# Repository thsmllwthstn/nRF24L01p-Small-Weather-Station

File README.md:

# Small Weather Station with nRF24L01+

For any nRF24L01+ project!

Vcc: 3.3V - 15V

### Description
Start a nRF24L01+ sensor network or expand your existing projects with this Small Weather Station!
This comes with easy to use example codes for Arduino and Raspberry Pi!

This station measures and sends:

 -Temperature
 
 -Humidity
 
 -Lightintensity

To achieve this the station uses three different sensors:

 -DS18B20: Digital temperature sensor
 
 -DHT11: Basic temperature and humidity sensor
 
 -LDR: Measures lightintensity

### What do you need?
You will need a Small Weather Station and your own nRF24L01+ receiver.
You can buy the Small Weather Station in the link below:

--ebay link

Or you can build your own station, you can find the schematics and source code in the link below:
https://github.com/thsmllwthstn/nRF24L01p-Small-Weather-Station/tree/master/station/station_basic

In the link below you will find an easy example code written for Arduino and Python 3 for receiving data from the station:
https://github.com/thsmllwthstn/nRF24L01p-Small-Weather-Station/tree/master/receiver

Simply copy and paste this code and you are ready to retreive data from the station!

### How does it work?
Power the Vin pin with 3V3 - 15V.

As soon as the onboard LED blinks 2 times in a row the station starts sending the data.

Use the example code to receive the data.

It sends the data every 5 seconds.

You can change the stations settings by pressing the button. The LED will go ON. The station is now in receiving mode.
There are 4 settings you can change:

 -Timer (rate at which the station sends the data in seconds)
 
 -Tranceive address
 
 -Receive address
 
 -Frequency

The example code explains in detail how to change these settings.

### Add a waterproof digital temperature sensor!
The station comes with 3 additional pins for connecting a waterproof DS18B20 temperature sensor.
Solder the Vcc, data and ground pins from the temperature sensor to the 3V3, data and GND pin from the station.
Once connected the station detects the presence of the added DS18B20 sensor.
The station will now send the standard readings with the added DS18B20 sensor!

### Programmable Small Weather Station?
Do you want full access to all the settings or use the station to control any other 3V3 circuit?
This is possible with a USBASP programmer and the programmable small weather station: 

--ebay link

Or you can build your own programmable station, you can find the schematics and source code in the link below:
https://github.com/thsmllwthstn/nRF24L01p-Small-Weather-Station/tree/master/station/station_basic_with_programmer

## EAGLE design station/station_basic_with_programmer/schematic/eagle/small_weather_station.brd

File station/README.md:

# Read me

Basic Small Weather Station:
--Foto1

Basic Small Weather Station with programmer:
--Foto2

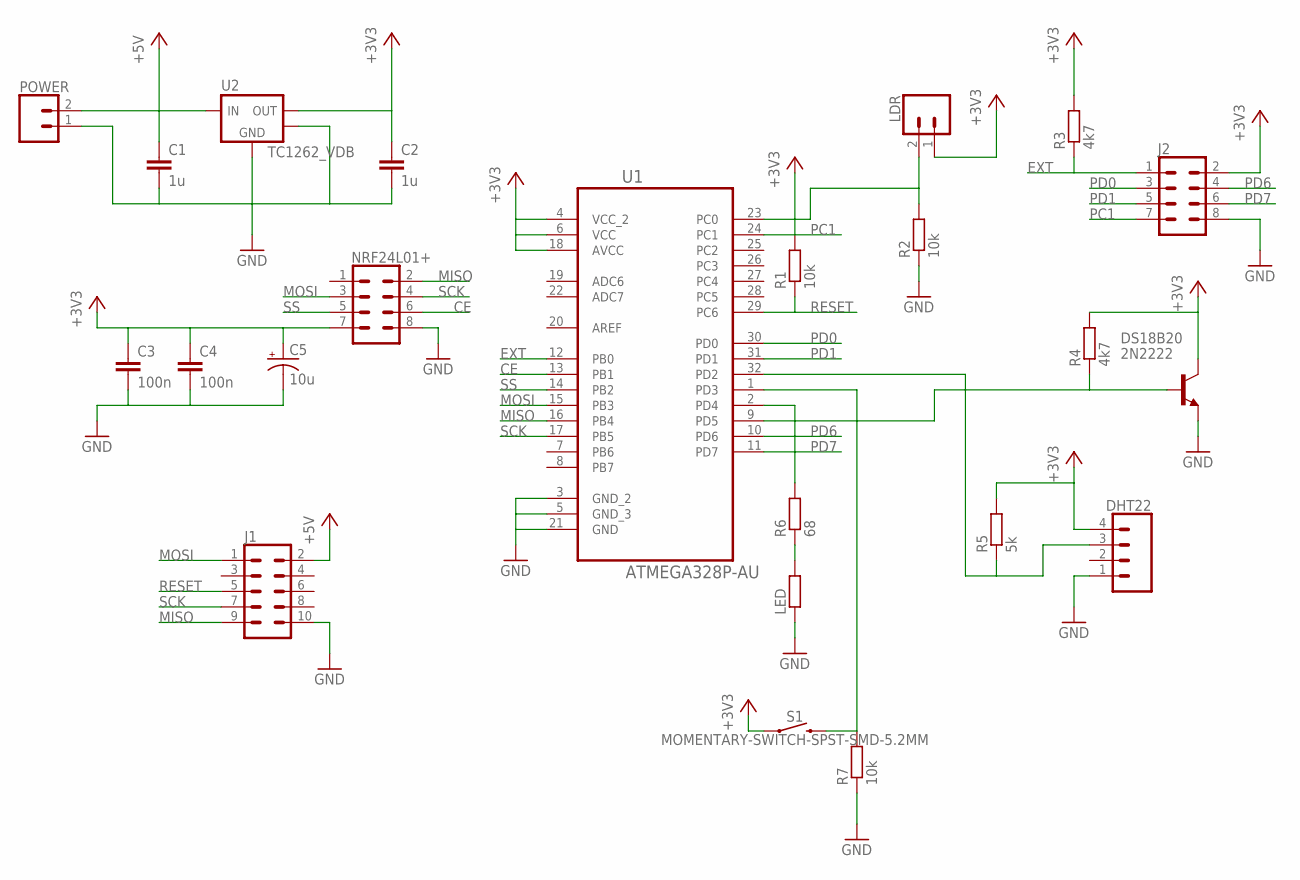
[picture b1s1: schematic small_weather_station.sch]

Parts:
C1, C2: 1u; C0402
C3, C4: 100n; C0402
C5: 10u; PANASONIC_D
DHT22: CONN_04; 1X04
DS18B20: 2N2222; TO92-EBC-OVAL
J1: CONN_05X2SHD-NS; 2X5-SHROUDED-NS
J2: CONN_04X2; 2X4
LDR: CONN_02; 1X02
LED: R-EU_R0402; R0402
NRF24L01+: CONN_04X2; 2X4
POWER: CONN_02; 1X02
R1, R2, R7: 10k; R0402
R3, R4: 4k7; R0402
R5: 5k; R0402
R6: 68; R0402
S1: MOMENTARY-SWITCH-SPST-SMD-5.2MM; TACTILE_SWITCH_SMD_5.2MM
U1: ATMEGA328P-AU; QFP80P900X900X120-32N
U2: TC1262_VDB; SOT-223-3

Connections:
+3V3: C2.1, C3.1, C4.1, C5.+, DHT22.4, DS18B20.C, J2.2, LDR.1, NRF24L01+.7, R1.2, R3.2, R4.2, R5.2, S1.1, U1.4 (VCC_2), U1.6 (VCC), U1.18 (AVCC), U2.3 (VOUT)
+5V: C1.1, J1.2, POWER.2, U2.1 (VIN)
CE: NRF24L01+.6, U1.13 (PB1)
EXT: J2.1, R3.1, U1.12 (PB0)
GND: C1.2, C2.2, C3.2, C4.2, C5.-, DHT22.1, DS18B20.E, J1.10, J2.8, LED.1, NRF24L01+.8, POWER.1, R2.1, R7.1, U1.3 (GND_2), U1.5 (GND_3), U1.21 (GND), U2.2 (GND), U2.4 (TAB)
MISO: J1.9, NRF24L01+.2, U1.16 (PB4)
MOSI: J1.1, NRF24L01+.3, U1.15 (PB3)
unnamed: R6.2, U1.2 (PD4)
unnamed: DHT22.3, R5.1, U1.32 (PD2)
unnamed: LDR.2, R2.2, U1.23 (PC0)
unnamed: DS18B20.B, R4.1, U1.9 (PD5)
unnamed: LED.2, R6.1
unnamed: R7.2, S1.3 (2), U1.1 (PD3)
PC1: J2.7, U1.24 (PC1)
PD0: J2.3, U1.30 (PD0)
PD1: J2.5, U1.31 (PD1)
PD6: J2.4, U1.10 (PD6)
PD7: J2.6, U1.11 (PD7)
RESET: J1.5, R1.1, U1.29 (PC6)
SCK: J1.7, NRF24L01+.4, U1.17 (PB5)
SS: NRF24L01+.5, U1.14 (PB2)

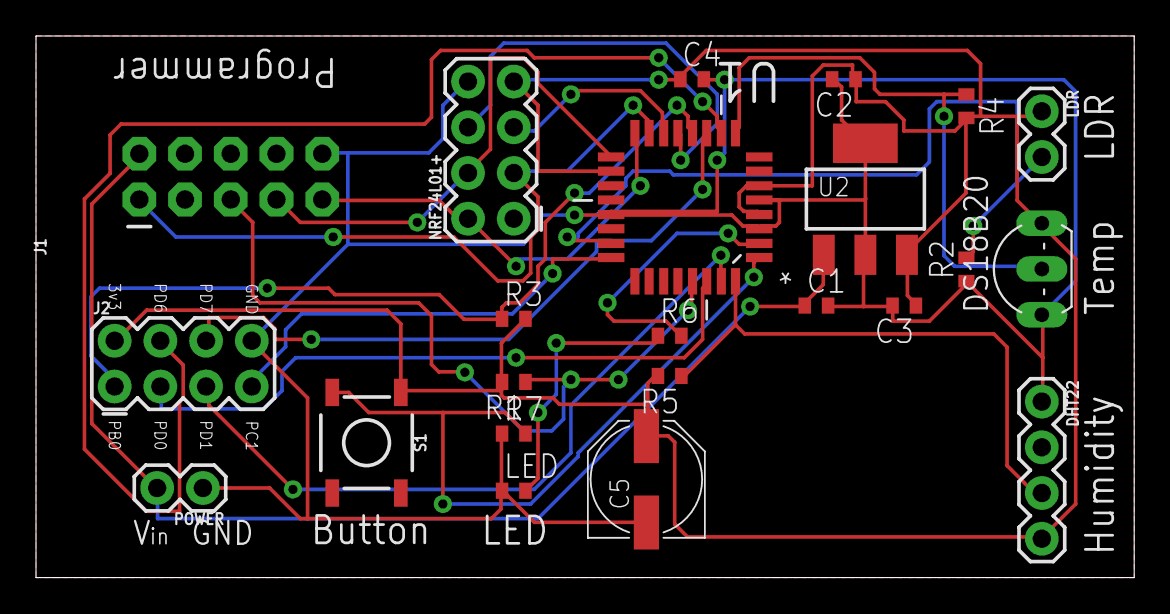
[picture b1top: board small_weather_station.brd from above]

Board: 2 copper layers, 61.0 x 30.1 mm, 23 parts (0 on the bottom side), 21 nets.

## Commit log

2018-01-01 arduino
    tested on arduino uno
2018-01-01 python
    tested on raspberry pi 3 mobel B
2018-01-01 python 3
    tested on raspberry pi 3 model b
2018-01-01 small_weather_station.b#1
2018-01-01 schematic
2018-01-01 Create test

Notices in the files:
parts and their libraries:
SparkFun-Switches: Licensing: Creative Commons ShareAlike 4.0 International - https://creativecommons.org/licenses/by-sa/4.0
